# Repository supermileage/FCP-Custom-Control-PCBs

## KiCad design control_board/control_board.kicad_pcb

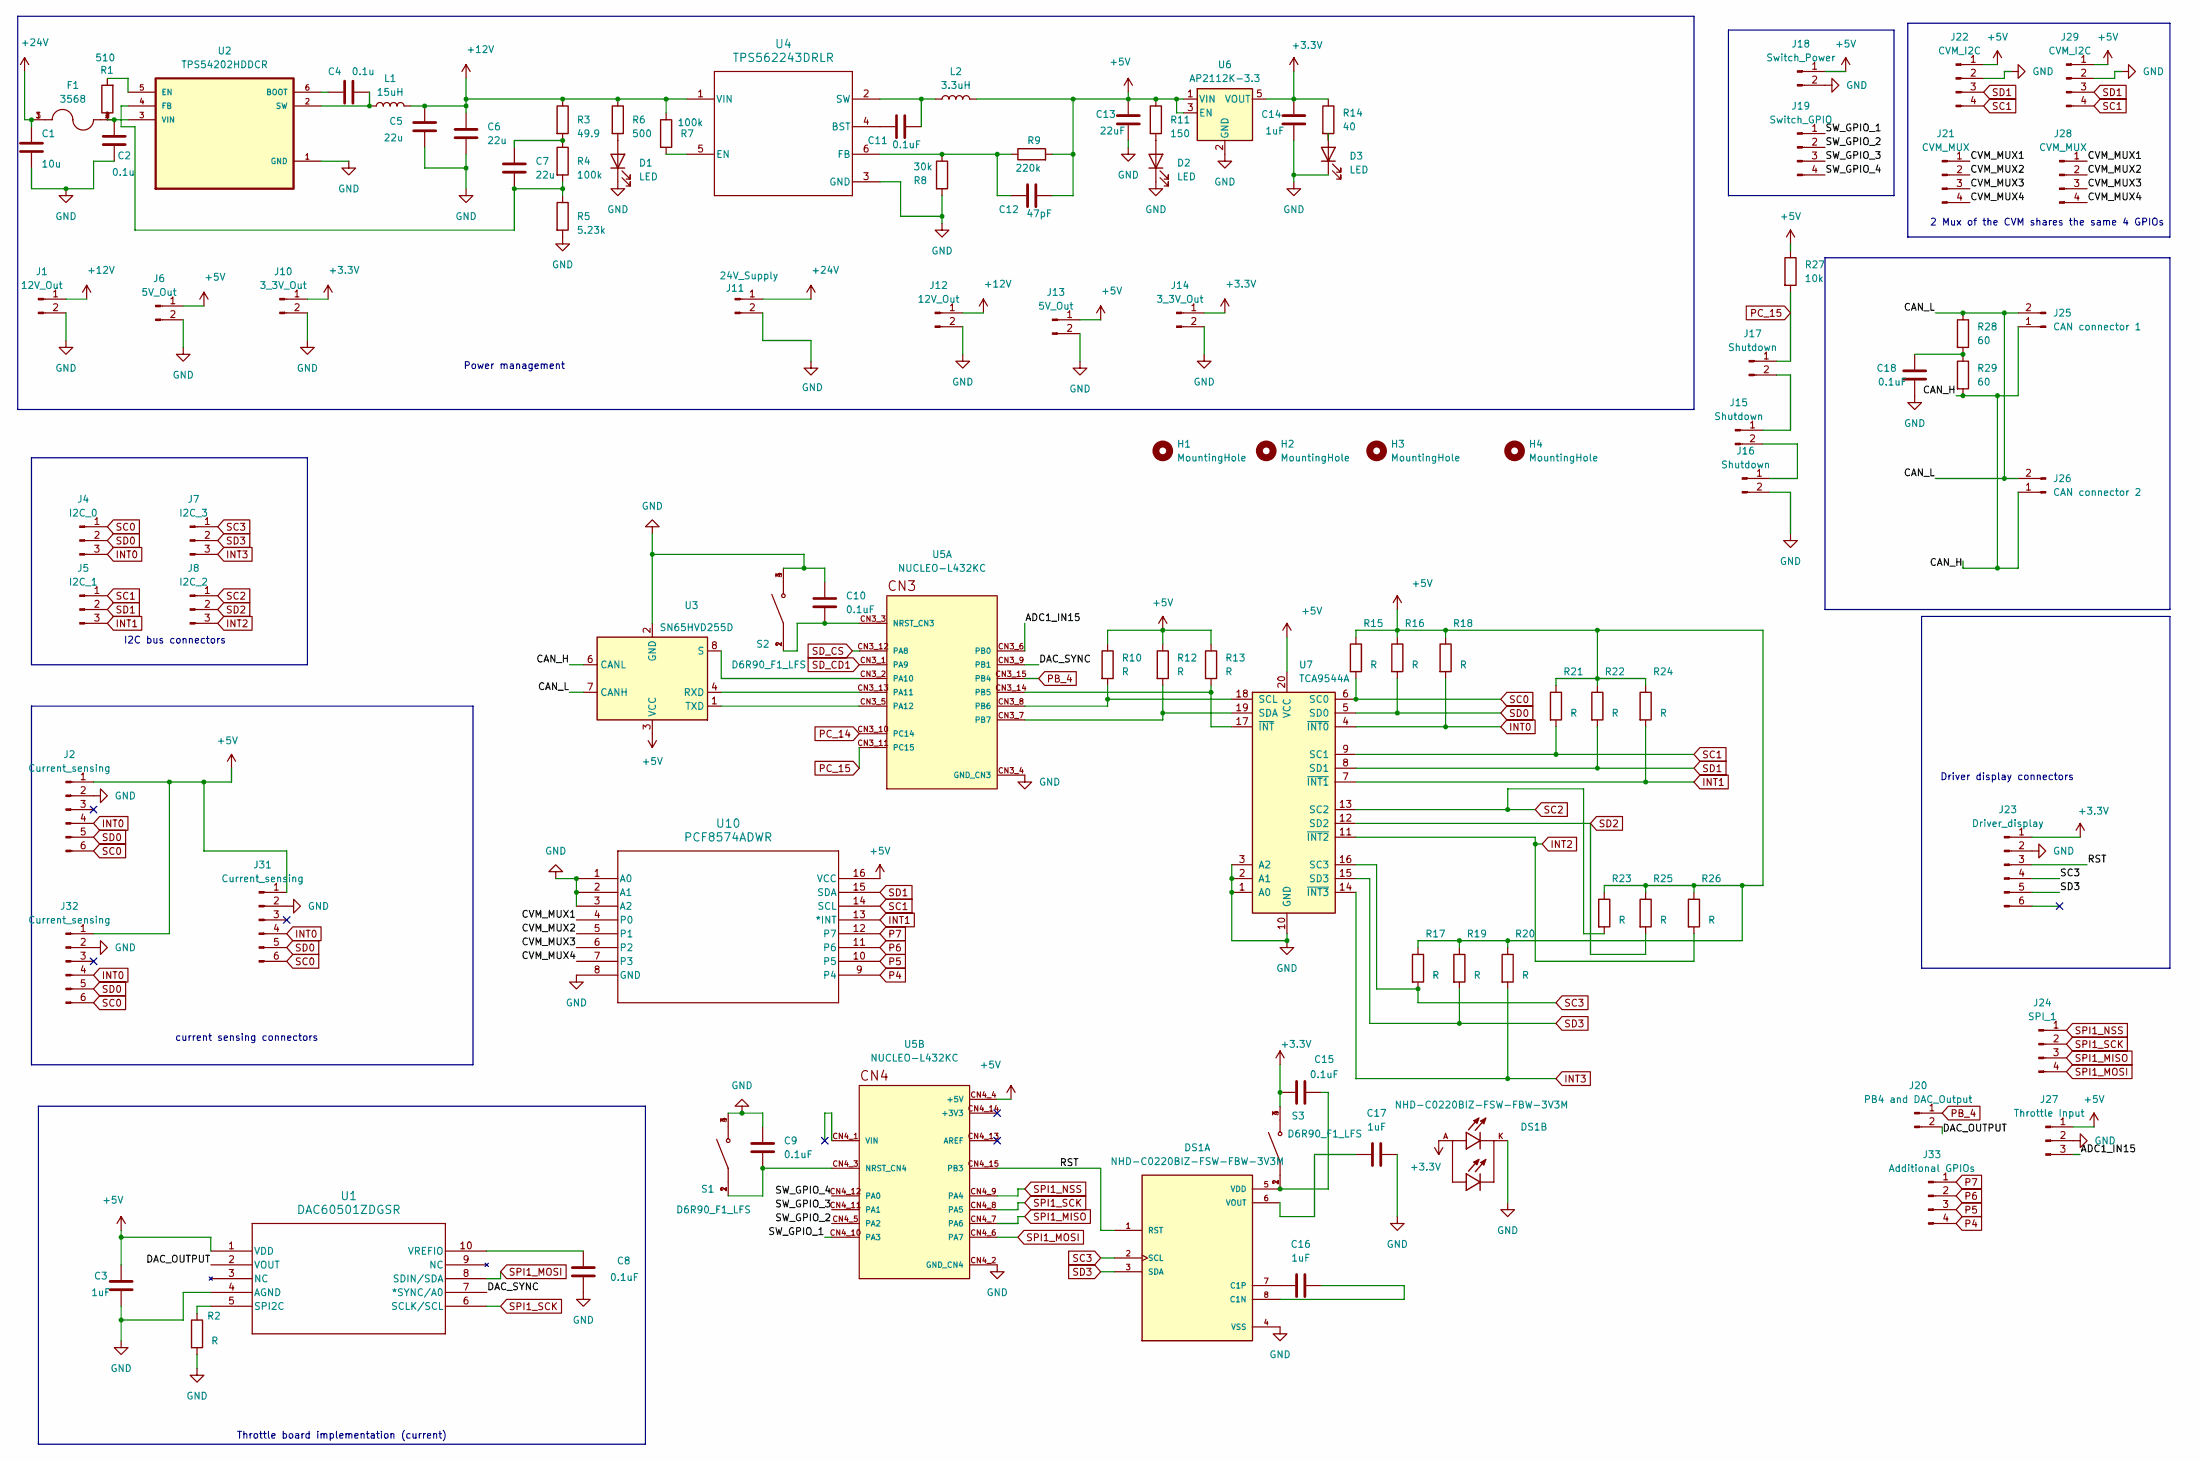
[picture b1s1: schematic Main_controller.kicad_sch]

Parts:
C1: 10u; C_0805_2012Metric
C2, C4: 0.1u; C_0805_2012Metric
C3, C14, C16, C17: 1uF; C_0805_2012Metric
C5, C6, C7: 22u; C_0805_2012Metric
C8, C9, C10, C11, C15, C18: 0.1uF; C_0805_2012Metric
C12: 47pF; C_0805_2012Metric
C13: 22uF; C_0805_2012Metric
D1, D2, D3: LED; LED_0805_2012Metric
DS1: NHD-C0220BIZ-FSW-FBW-3V3M; LCD_NHD-C0220BIZ-FSW-FBW-3V3M; PARTREV 1.0
F1: 3568; FUSE_3568; PARTREV C
H1, H2, H3, H4: MountingHole; MountingHole_5.3mm_M5_DIN965_Pad
J1, J12: 12V_Out; MOLEX_2125280200
J2, J31, J32: Current_sensing; CONN_2125280000_06_MOL
J4: I2C_0; CONN_SDA-70543-xxxx_04_MOL
J5: I2C_1; CONN_SDA-70543-XXXX_03_MOL
J6, J13: 5V_Out; MOLEX_2125280200
J7: I2C_3; CONN_SDA-70543-XXXX_03_MOL
J8: I2C_2; CONN_SDA-70543-XXXX_03_MOL
J10, J14: 3_3V_Out; MOLEX_2125280200
J11: 24V_Supply; MOLEX_2125280200
J15, J16, J17: Shutdown; CONN_SDA-70543-xxxx_02_MOL
J18: Switch_Power; MOLEX_2125280200
J19: Switch_GPIO; CONN_2125280000_04_MOL
J20: PB4 and DAC_Output; MOLEX_2125280200
J21, J28: CVM_MUX; CONN_2125280000_04_MOL
J22, J29: CVM_I2C; CONN_2125280000_04_MOL
J23: Driver_display; CONN_2125280000_06_MOL
J24: SPI_1; CONN_SDA-70543-XXXX_04_MOL
J25: CAN connector 1; MOLEX_2125280200
J26: CAN connector 2; MOLEX_2125280200
J27: Throttle Input; CONN_SDA-70543-XXXX_03_MOL
J33: Additional GPIOs; CONN_SDA-70543-xxxx_04_MOL
L1: 15uH; IND_2012_TDK
L2: 3.3uH; L_1008_2520Metric
R1: 510; R_0805_2012Metric
R2, R10, R12, R13, R15, R16, R17, R18, R19, R20, R21, R22, R23, R24, R25, R26: R; R_0805_2012Metric
R3: 49.9; R_0805_2012Metric
R4, R7: 100k; R_0805_2012Metric
R5: 5.23k; R_0805_2012Metric
R6: 500; R_0805_2012Metric
R8: 30k; R_0805_2012Metric
R9: 220k; R_0805_2012Metric
R11: 150; R_0805_2012Metric
R14: 40; R_0805_2012Metric
R27: 10k; R_0805_2012Metric
R28, R29: 60; R_0805_2012Metric
S1, S2, S3: D6R90_F1_LFS; SW_D6R90_F1_LFS; PARTREV N/A
U1: DAC60501ZDGSR; DGS10_TEX-L
U2: TPS54202HDDCR; SOT95P280X110-6N
U3: SN65HVD255D; SOIC-8_3.9x4.9mm_P1.27mm
U4: TPS562243DRLR; DRL0006A-MFG
U5: NUCLEO-L432KC; MODULE_NUCLEO-L432KC; PARTREV N/A; DigiKey_Part_Number 497-16592-ND
U6: AP2112K-3.3; SOT-23-5
U7: TCA9544A; TSSOP-20_4.4x6.5mm_P0.65mm
U10: PCF8574ADWR; DW16

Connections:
+3.3V: C14.1, C15.2, DS1.A, J10.1, J14.1, J23.1, R14.1, S3.3, S3.4, U6.5 (VOUT); also elsewhere on the board
+5V: C3.2, C12.2, C13.1, J2.1, J6.1, J13.1, J18.1, J22.1, J27.1, J29.1, J31.1, J32.1, L2.2, R9.2, R10.1, R11.1, R12.1, R13.1, R15.1, R16.1, R17.1, R18.1, R19.1, R20.1, R21.1, R22.1, R23.1, R24.1, R25.1, R26.1, R27.1, U1.1 (VDD), U3.3 (VCC), U5.CN4_4 (+5V), U6.1 (VIN), U6.3 (EN), U7.20 (VCC), U10.16 (VCC); also elsewhere on the board
+12V: C5.1, C6.1, J1.1, J12.1, L1.2, R3.1, R6.1, R7.1, U4.1 (VIN)
+24V: C1.1, F1.1, F1.3, J11.1
/Main_controller/ADC1_IN15: J27.3, U5.CN3_6 (PB0)
/Main_controller/CAN_H: J25.1, J26.1, R29.2, U3.6 (CANL)
/Main_controller/CAN_L: J25.2, J26.2, R28.1, U3.7 (CANH)
/Main_controller/CVM_MUX1: J21.1, J28.1, U10.4 (P0)
/Main_controller/CVM_MUX2: J21.2, J28.2, U10.5 (P1)
/Main_controller/CVM_MUX3: J21.3, J28.3, U10.6 (P2)
/Main_controller/CVM_MUX4: J21.4, J28.4, U10.7 (P3)
/Main_controller/DAC_OUTPUT: J20.2, U1.2 (VOUT)
/Main_controller/DAC_SYNC: U1.7 (*SYNC/A0), U5.CN3_9 (PB1)
/Main_controller/RST: DS1.1 (RST), J23.3, U5.CN4_15 (PB3)
/Main_controller/SW_GPIO_1: J19.1, U5.CN4_10 (PA3)
/Main_controller/SW_GPIO_2: J19.2, U5.CN4_5 (PA2)
/Main_controller/SW_GPIO_3: J19.3, U5.CN4_11 (PA1)
/Main_controller/SW_GPIO_4: J19.4, U5.CN4_12 (PA0)
GND: C1.2, C2.2, C3.1, C5.2, C6.2, C8.1, C9.2, C10.2, C13.2, C14.2, C17.2, C18.2, D1.1 (K), D2.1 (K), D3.1 (K), DS1.4 (VSS), DS1.K, J1.2, J2.2, J6.2, J10.2, J11.2, J12.2, J13.2, J14.2, J16.2, J18.2, J22.2, J23.2, J27.2, J29.2, J31.2, J32.2, R2.2, R5.2, R8.2, S1.3, S1.4, S2.3, S2.4, U1.4 (AGND), U2.1 (GND), U3.2 (GND), U4.3 (GND), U5.CN3_4 (GND_CN3), U5.CN4_2 (GND_CN4), U6.2 (GND), U7.1 (A0), U7.2 (A1), U7.3 (A2), U7.10 (GND), U10.1 (A0), U10.2 (A1), U10.3 (A2), U10.8 (GND); also elsewhere on the board
INT0: J2.4, J4.3, J31.4, J32.4, R18.2, U7.4 (~INT0)
INT1: J5.3, R24.2, U7.7 (~INT1), U10.13 (*INT)
INT2: J8.3, R26.2, U7.11 (~INT2)
INT3: J7.3, R20.2, U7.14 (~INT3)
unnamed: C7.1, R3.2, R4.1
unnamed: C18.1, R28.2, R29.1
unnamed: D1.2 (A), R6.2
unnamed: D2.2 (A), R11.2
unnamed: D3.2 (A), R14.2
unnamed: C16.2, DS1.8 (C1N)
unnamed: C16.1, DS1.7 (C1P)
unnamed: C15.1, DS1.5 (VDD), S3.1, S3.2
unnamed: C17.1, DS1.6 (VOUT)
unnamed: J15.1, J17.2
unnamed: J15.2, J16.1
unnamed: R2.1, U1.5 (SPI2C)
unnamed: C8.2, U1.10 (VREFIO)
unnamed: C4.1, U2.6 (BOOT)
unnamed: R1.2, U2.5 (EN)
unnamed: C7.2, R4.2, R5.1, U2.4 (FB)
unnamed: C4.2, L1.1, U2.2 (SW)
unnamed: C2.1, F1.2, F1.4, R1.1, U2.3 (VIN)
unnamed: U3.4 (RXD), U5.CN3_13 (PA11)
unnamed: U3.8 (S), U5.CN3_2 (PA10)
unnamed: U3.1 (TXD), U5.CN3_5 (PA12)
unnamed: C11.1, U4.4 (BST)
unnamed: R7.2, U4.5 (EN)
unnamed: C12.1, R8.1, R9.1, U4.6 (FB)
unnamed: C11.2, L2.1, U4.2 (SW)
unnamed: C10.1, S2.1, S2.2, U5.CN3_3 (NRST_CN3)
unnamed: R13.2, U5.CN3_14 (PB5), U7.17 (~INT)
unnamed: R10.2, U5.CN3_8 (PB6), U7.18 (SCL)
unnamed: R12.2, U5.CN3_7 (PB7), U7.19 (SDA)
unnamed: C9.1, S1.1, S1.2, U5.CN4_3 (NRST_CN4)
P4: J33.4, U10.9 (P4)
P5: J33.3, U10.10 (P5)
P6: J33.2, U10.11 (P6)
P7: J33.1, U10.12 (P7)
PB_4: J20.1, U5.CN3_15 (PB4)
PC_14: U5.CN3_10 (PC14); also elsewhere on the board
PC_15: J17.1, R27.2, U5.CN3_11 (PC15)
SC0: J2.6, J4.1, J31.6, J32.6, R15.2, U7.6 (SC0)
SC1: J5.1, J22.4, J29.4, R21.2, U7.9 (SC1), U10.14 (SCL)
SC2: J8.1, R23.2, U7.13 (SC2); also elsewhere on the board
SC3: DS1.2 (SCL), J7.1, J23.4, R17.2, U7.16 (SC3)
SD0: J2.5, J4.2, J31.5, J32.5, R16.2, U7.5 (SD0)
SD1: J5.2, J22.3, J29.3, R22.2, U7.8 (SD1), U10.15 (SDA)
SD2: J8.2, R25.2, U7.12 (SD2); also elsewhere on the board
SD3: DS1.3 (SDA), J7.2, J23.5, R19.2, U7.15 (SD3)
SD_CD1: U5.CN3_1 (PA9); also elsewhere on the board
SD_CS: U5.CN3_12 (PA8); also elsewhere on the board
SPI1_MISO: J24.3, U5.CN4_7 (PA6); also elsewhere on the board
SPI1_MOSI: J24.4, U1.8 (SDIN/SDA), U5.CN4_6 (PA7); also elsewhere on the board
SPI1_NSS: J24.1, U5.CN4_9 (PA4)
SPI1_SCK: J24.2, U1.6 (SCLK/SCL), U5.CN4_8 (PA5); also elsewhere on the board

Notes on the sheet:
I2C bus connectors
Power management
current sensing connectors
Driver display connectors
2 Mux of the CVM shares the same 4 GPIOs
Throttle board implementation (current)

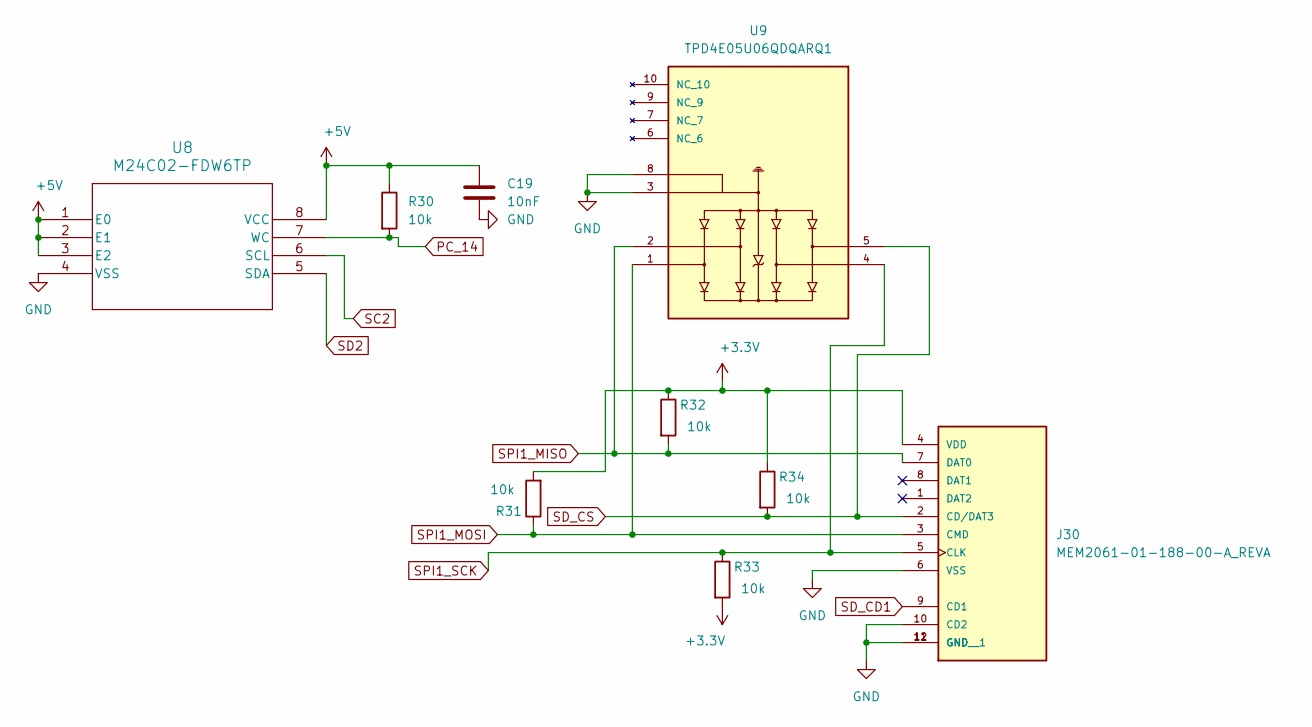
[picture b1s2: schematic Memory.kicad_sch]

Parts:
C19: 10nF; C_0805_2012Metric
J30: MEM2061-01-188-00-A_REVA; GCT_MEM2061-01-188-00-A_REVA
R30, R31, R32, R33, R34: 10k; R_0805_2012Metric
U8: M24C02-FDW6TP; TSSOP8_M24C02_STM
U9: TPD4E05U06QDQARQ1; IC_TPD4E05U06QDQARQ1; PARTREV F

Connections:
+3.3V: J30.4 (VDD), R31.2, R32.1, R33.2, R34.1; also elsewhere on the board
+5V: C19.1, R30.1, U8.1 (E0), U8.2 (E1), U8.3 (E2), U8.8 (VCC); also elsewhere on the board
GND: C19.2, J30.6 (VSS), J30.10 (CD2), J30.11 (GND), J30.12 (GND__1), U8.4 (VSS), U9.3, U9.8; also elsewhere on the board
PC_14: R30.2, U8.7 (WC); also elsewhere on the board
SC2: U8.6 (SCL); also elsewhere on the board
SD2: U8.5 (SDA); also elsewhere on the board
SD_CD1: J30.9 (CD1); also elsewhere on the board
SD_CS: J30.2 (CD/DAT3), R34.2, U9.5; also elsewhere on the board
SPI1_MISO: J30.7 (DAT0), R32.2, U9.2; also elsewhere on the board
SPI1_MOSI: J30.3 (CMD), R31.1, U9.1; also elsewhere on the board
SPI1_SCK: J30.5 (CLK), R33.1, U9.4; also elsewhere on the board

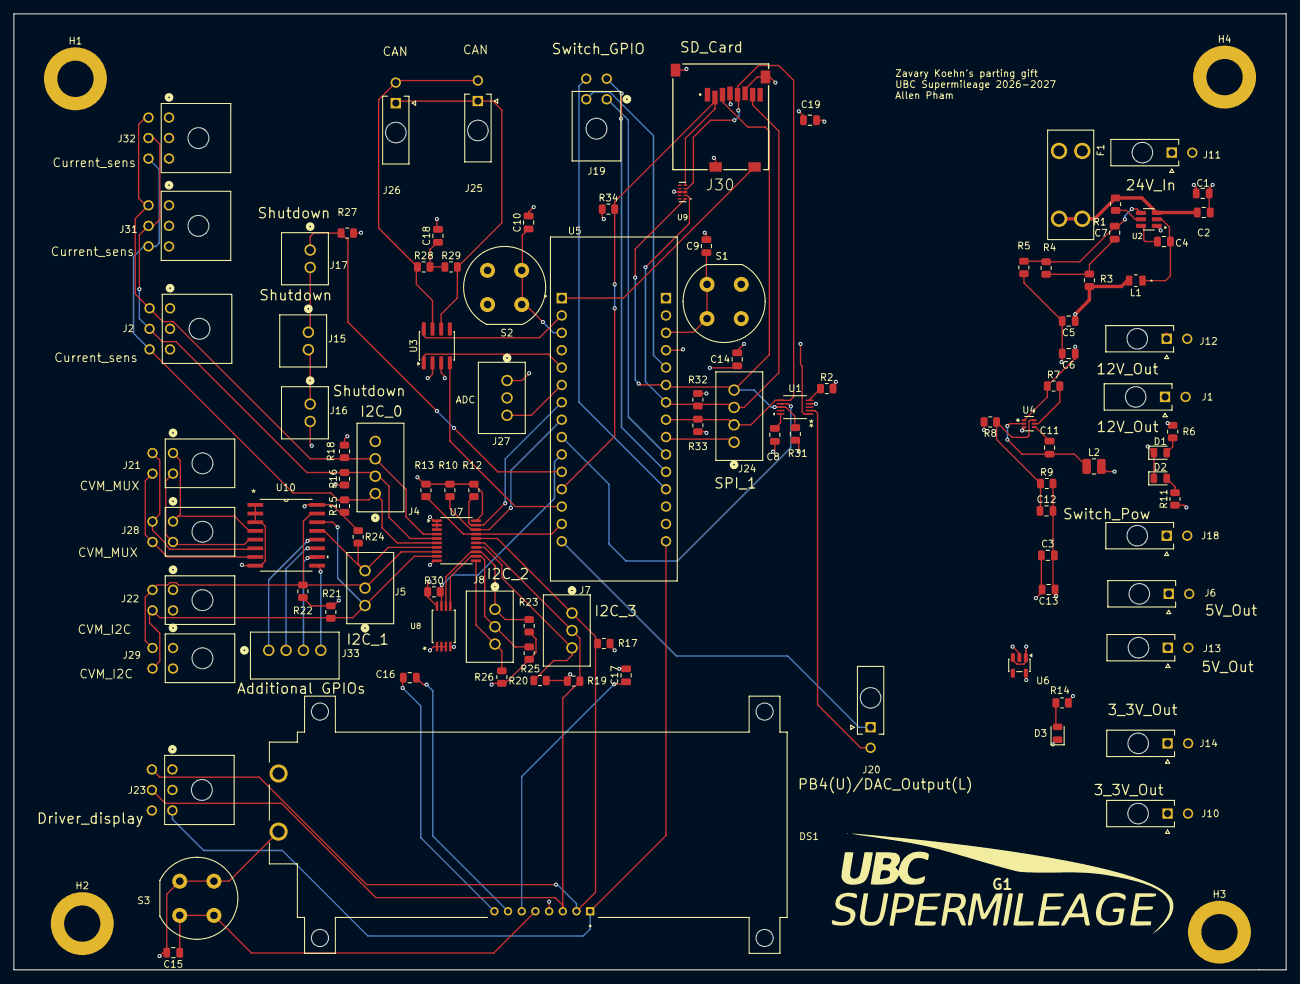
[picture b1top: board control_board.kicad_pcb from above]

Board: 4 copper layers, 186.0 x 139.8 mm, 109 parts (0 on the bottom side), 74 nets.

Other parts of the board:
G1: LOGO

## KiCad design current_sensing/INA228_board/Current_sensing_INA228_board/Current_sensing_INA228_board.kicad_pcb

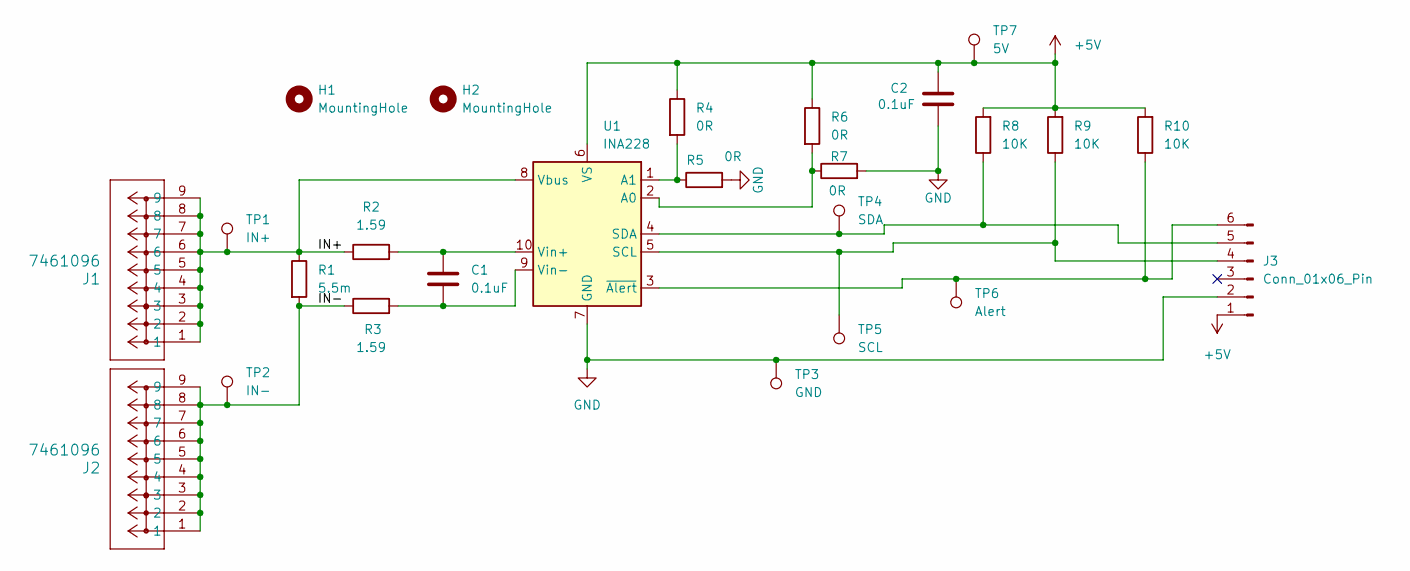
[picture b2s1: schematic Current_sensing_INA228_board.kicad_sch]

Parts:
C1, C2: 0.1uF; C_0402_1005Metric
H1, H2: MountingHole; MountingHole_4.3mm_M4_DIN965
J1, J2: 7461096; CONN9_1096_WRE
J3: Conn_01x06_Pin; CONN_2125280000_06_MOL
R1: 5.5m; R_0603_1608Metric
R2, R3: 1.59; R_0603_1608Metric
R4, R5, R6, R7: 0R; R_0603_1608Metric
R8, R9, R10: 10K; R_0603_1608Metric
TP1: IN+; TestPoint_Keystone_5000-5004_Miniature
TP2: IN-; TestPoint_Keystone_5000-5004_Miniature
TP3: GND; TestPoint_Keystone_5000-5004_Miniature
TP4: SDA; TestPoint_Keystone_5000-5004_Miniature
TP5: SCL; TestPoint_Keystone_5000-5004_Miniature
TP6: Alert; TestPoint_Keystone_5000-5004_Miniature
TP7: 5V; TestPoint_Keystone_5000-5004_Miniature
U1: INA228; VSSOP-10_3x3mm_P0.5mm

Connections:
+5V: C2.1, J3.1, R4.1, R6.1, R8.2, R9.2, R10.2, TP7.1, U1.6 (VS)
/IN+: J1.1, J1.2, J1.3, J1.4, J1.5, J1.6, J1.7, J1.8, J1.9, R1.1, R2.1, TP1.1, U1.8 (Vbus)
/IN-: J2.1, J2.2, J2.3, J2.4, J2.5, J2.6, J2.7, J2.8, J2.9, R1.2, R3.1, TP2.1
GND: C2.2, J3.2, R5.2, R7.2, TP3.1, U1.7 (GND)
unnamed: J3.4, R9.1, TP5.1, U1.5 (SCL)
unnamed: J3.5, R8.1, TP4.1, U1.4 (SDA)
unnamed: J3.6, R10.1, TP6.1, U1.3 (~Alert)
unnamed: R6.2, R7.1, U1.2 (A0)
unnamed: R4.2, R5.1, U1.1 (A1)
unnamed: C1.1, R2.2, U1.10 (Vin+)
unnamed: C1.2, R3.2, U1.9 (Vin-)

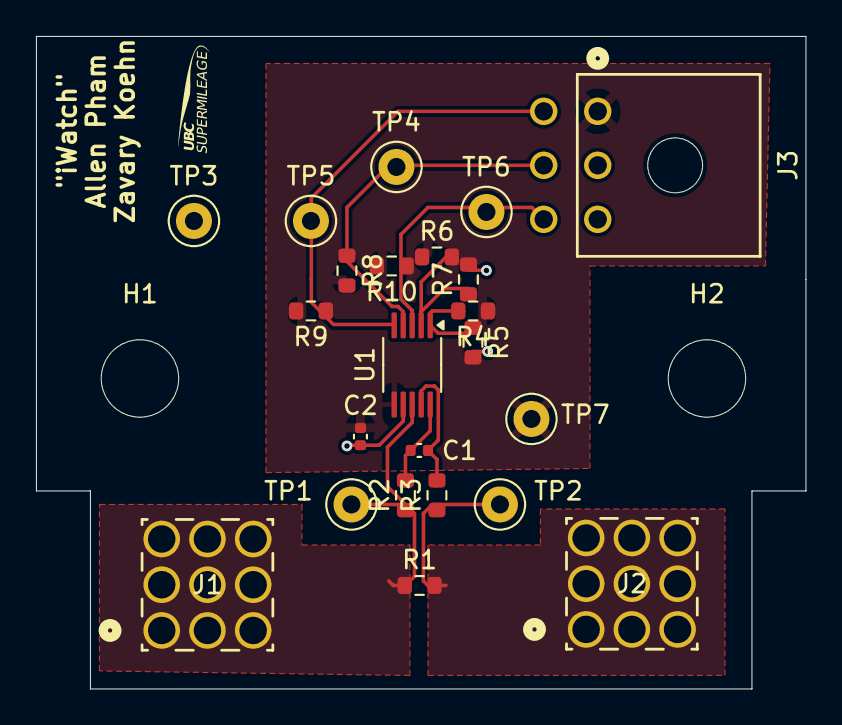
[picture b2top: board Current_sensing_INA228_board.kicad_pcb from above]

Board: 2 copper layers, 42.8 x 36.2 mm, 25 parts (0 on the bottom side), 11 nets.

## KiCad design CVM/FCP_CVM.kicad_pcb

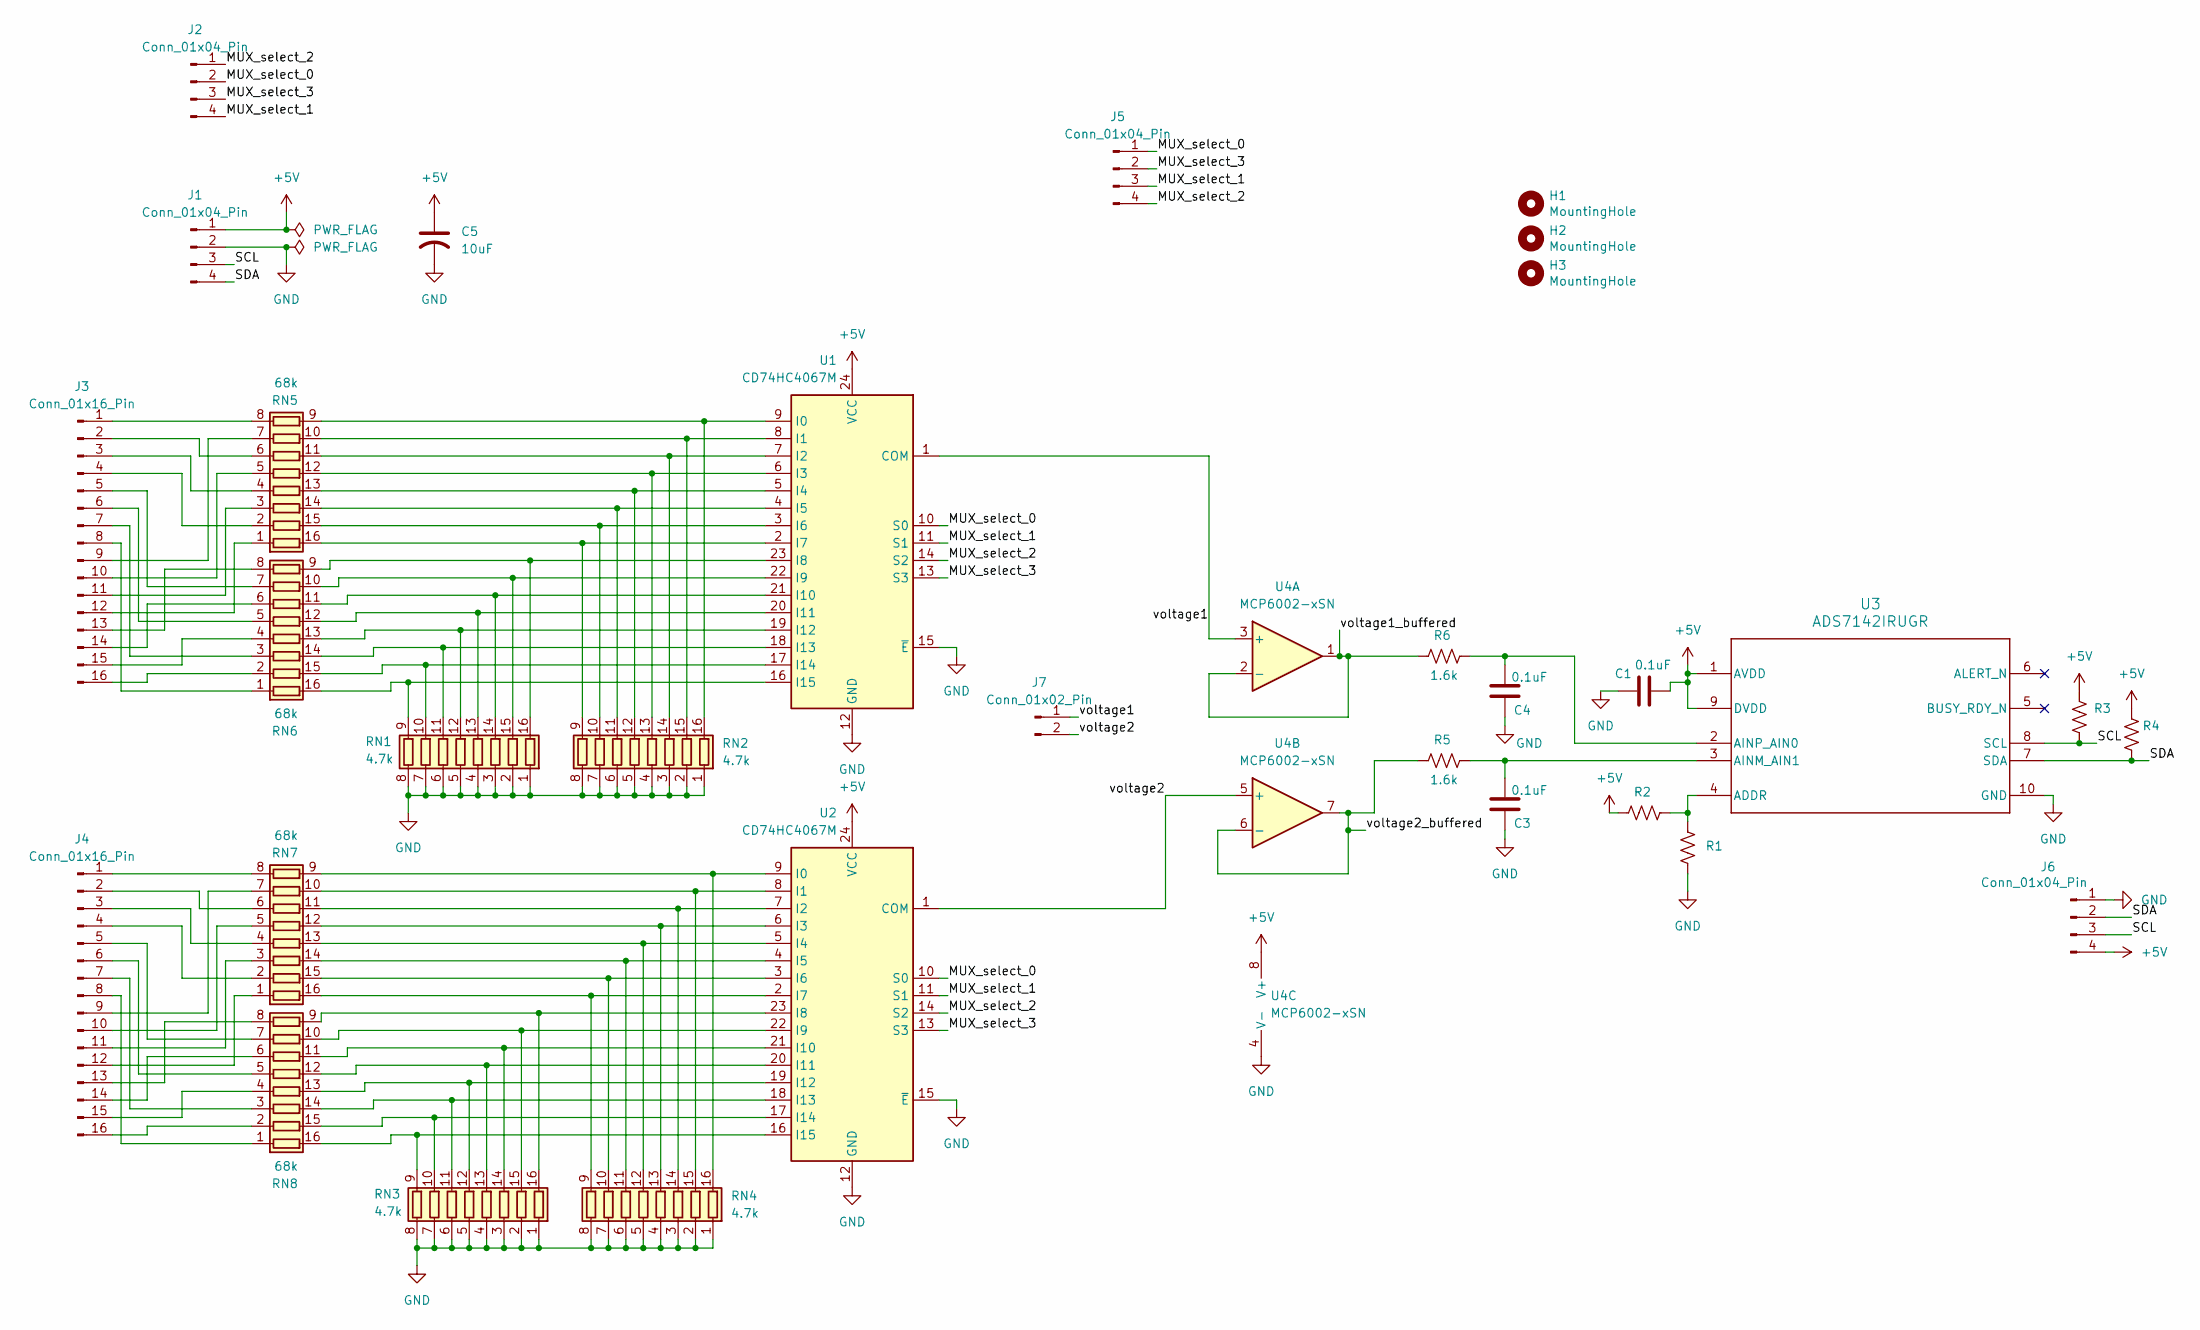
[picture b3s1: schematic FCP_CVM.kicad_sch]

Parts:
C1, C3, C4: 0.1uF; C_0805_2012Metric_Pad1.18x1.45mm_HandSolder
C5: 10uF; WCAP-ASLI_4X5.5_DXL_
H1, H2, H3: MountingHole; MountingHole_3.2mm_M3
J1, J2: Conn_01x04_Pin; MOLEX_2125280400
J3, J4: Conn_01x16_Pin; AMPHENOL_10127720-162LF
J5, J6: Conn_01x04_Pin; PinHeader_1x04_P2.54mm_Vertical
J7: Conn_01x02_Pin; PinHeader_1x02_P2.54mm_Vertical
R1, R2, R3, R4: R_US; R_0805_2012Metric_Pad1.20x1.40mm_HandSolder
R5, R6: 1.6k; R_0805_2012Metric_Pad1.20x1.40mm_HandSolder
RN1, RN2, RN3, RN4: 4.7k; RES_EXB2HV
RN5, RN6, RN7, RN8: 68k; RES_EXB2HV
U1, U2: CD74HC4067M; SOIC-24W_7.5x15.4mm_P1.27mm
U3: ADS7142IRUGR; RUG0010A
U4: MCP6002-xSN; SOIC-8_3.9x4.9mm_P1.27mm

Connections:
+5V: C1.1, C5.1, J1.1, J6.4, R2.2, R3.1, R4.1, U1.24 (VCC), U2.24 (VCC), U3.1 (AVDD), U3.9 (DVDD), U4.8 (V+)
/MUX_select_0: J2.2, J5.1, U1.10 (S0), U2.10 (S0)
/MUX_select_1: J2.4, J5.3, U1.11 (S1), U2.11 (S1)
/MUX_select_2: J2.1, J5.4, U1.14 (S2), U2.14 (S2)
/MUX_select_3: J2.3, J5.2, U1.13 (S3), U2.13 (S3)
/SCL: J1.3, J6.3, R3.2, U3.8 (SCL)
/SDA: J1.4, J6.2, R4.2, U3.7 (SDA)
/voltage1: J7.1, U1.1 (COM), U4.3 (+)
/voltage1_buffered: R6.2, U4.1, U4.2 (-)
/voltage2: J7.2, U2.1 (COM), U4.5 (+)
/voltage2_buffered: R5.2, U4.6 (-), U4.7
GND: C1.2, C3.2, C4.2, C5.2, J1.2, J6.1, R1.2, RN1.1 (R1.1), RN1.2 (R2.1), RN1.3 (R3.1), RN1.4 (R4.1), RN1.5 (R5.1), RN1.6 (R6.1), RN1.7 (R7.1), RN1.8 (R8.1), RN2.1 (R1.1), RN2.2 (R2.1), RN2.3 (R3.1), RN2.4 (R4.1), RN2.5 (R5.1), RN2.6 (R6.1), RN2.7 (R7.1), RN2.8 (R8.1), RN3.1 (R1.1), RN3.2 (R2.1), RN3.3 (R3.1), RN3.4 (R4.1), RN3.5 (R5.1), RN3.6 (R6.1), RN3.7 (R7.1), RN3.8 (R8.1), RN4.1 (R1.1), RN4.2 (R2.1), RN4.3 (R3.1), RN4.4 (R4.1), RN4.5 (R5.1), RN4.6 (R6.1), RN4.7 (R7.1), RN4.8 (R8.1), U1.12 (GND), U1.15 (~E), U2.12 (GND), U2.15 (~E), U3.10 (GND), U4.4 (V-)
unnamed: J3.1, RN5.8 (R8.1)
unnamed: J3.2, RN5.6 (R6.1)
unnamed: J3.3, RN5.4 (R4.1)
unnamed: J3.4, RN5.2 (R2.1)
unnamed: J3.5, RN6.7 (R7.1)
unnamed: J3.6, RN6.5 (R5.1)
unnamed: J3.7, RN6.3 (R3.1)
unnamed: J3.8, RN6.1 (R1.1)
unnamed: J3.9, RN5.7 (R7.1)
unnamed: J3.10, RN5.5 (R5.1)
unnamed: J3.11, RN5.3 (R3.1)
unnamed: J3.12, RN5.1 (R1.1)
unnamed: J3.13, RN6.8 (R8.1)
unnamed: J3.14, RN6.6 (R6.1)
unnamed: J3.15, RN6.4 (R4.1)
unnamed: J3.16, RN6.2 (R2.1)
unnamed: J4.1, RN7.8 (R8.1)
unnamed: J4.2, RN7.6 (R6.1)
unnamed: J4.3, RN7.4 (R4.1)
unnamed: J4.4, RN7.2 (R2.1)
unnamed: J4.5, RN8.7 (R7.1)
unnamed: J4.6, RN8.5 (R5.1)
unnamed: J4.7, RN8.3 (R3.1)
unnamed: J4.8, RN8.1 (R1.1)
unnamed: J4.9, RN7.7 (R7.1)
unnamed: J4.10, RN7.5 (R5.1)
unnamed: J4.11, RN7.3 (R3.1)
unnamed: J4.12, RN7.1 (R1.1)
unnamed: J4.13, RN8.8 (R8.1)
unnamed: J4.14, RN8.6 (R6.1)
unnamed: J4.15, RN8.4 (R4.1)
unnamed: J4.16, RN8.2 (R2.1)
unnamed: RN1.16 (R1.2), RN6.9 (R8.2), U1.23 (I8)
unnamed: RN1.15 (R2.2), RN6.10 (R7.2), U1.22 (I9)
unnamed: RN1.14 (R3.2), RN6.11 (R6.2), U1.21 (I10)
unnamed: RN1.13 (R4.2), RN6.12 (R5.2), U1.20 (I11)
unnamed: RN1.12 (R5.2), RN6.13 (R4.2), U1.19 (I12)
unnamed: RN1.11 (R6.2), RN6.14 (R3.2), U1.18 (I13)
unnamed: RN1.10 (R7.2), RN6.15 (R2.2), U1.17 (I14)
unnamed: RN1.9 (R8.2), RN6.16 (R1.2), U1.16 (I15)
unnamed: RN2.16 (R1.2), RN5.9 (R8.2), U1.9 (I0)
unnamed: RN2.15 (R2.2), RN5.10 (R7.2), U1.8 (I1)
unnamed: RN2.14 (R3.2), RN5.11 (R6.2), U1.7 (I2)
unnamed: RN2.13 (R4.2), RN5.12 (R5.2), U1.6 (I3)
unnamed: RN2.12 (R5.2), RN5.13 (R4.2), U1.5 (I4)
unnamed: RN2.11 (R6.2), RN5.14 (R3.2), U1.4 (I5)
unnamed: RN2.10 (R7.2), RN5.15 (R2.2), U1.3 (I6)
unnamed: RN2.9 (R8.2), RN5.16 (R1.2), U1.2 (I7)
unnamed: RN3.16 (R1.2), RN8.9 (R8.2), U2.23 (I8)
unnamed: RN3.15 (R2.2), RN8.10 (R7.2), U2.22 (I9)
unnamed: RN3.14 (R3.2), RN8.11 (R6.2), U2.21 (I10)
unnamed: RN3.13 (R4.2), RN8.12 (R5.2), U2.20 (I11)
unnamed: RN3.12 (R5.2), RN8.13 (R4.2), U2.19 (I12)
unnamed: RN3.11 (R6.2), RN8.14 (R3.2), U2.18 (I13)
unnamed: RN3.10 (R7.2), RN8.15 (R2.2), U2.17 (I14)
unnamed: RN3.9 (R8.2), RN8.16 (R1.2), U2.16 (I15)
unnamed: RN4.16 (R1.2), RN7.9 (R8.2), U2.9 (I0)
unnamed: RN4.15 (R2.2), RN7.10 (R7.2), U2.8 (I1)
unnamed: RN4.14 (R3.2), RN7.11 (R6.2), U2.7 (I2)
unnamed: RN4.13 (R4.2), RN7.12 (R5.2), U2.6 (I3)
unnamed: RN4.12 (R5.2), RN7.13 (R4.2), U2.5 (I4)
unnamed: RN4.11 (R6.2), RN7.14 (R3.2), U2.4 (I5)
unnamed: RN4.10 (R7.2), RN7.15 (R2.2), U2.3 (I6)
unnamed: RN4.9 (R8.2), RN7.16 (R1.2), U2.2 (I7)
unnamed: R1.1, R2.1, U3.4 (ADDR)
unnamed: C3.1, R5.1, U3.3 (AINM_AIN1)
unnamed: C4.1, R6.1, U3.2 (AINP_AIN0)

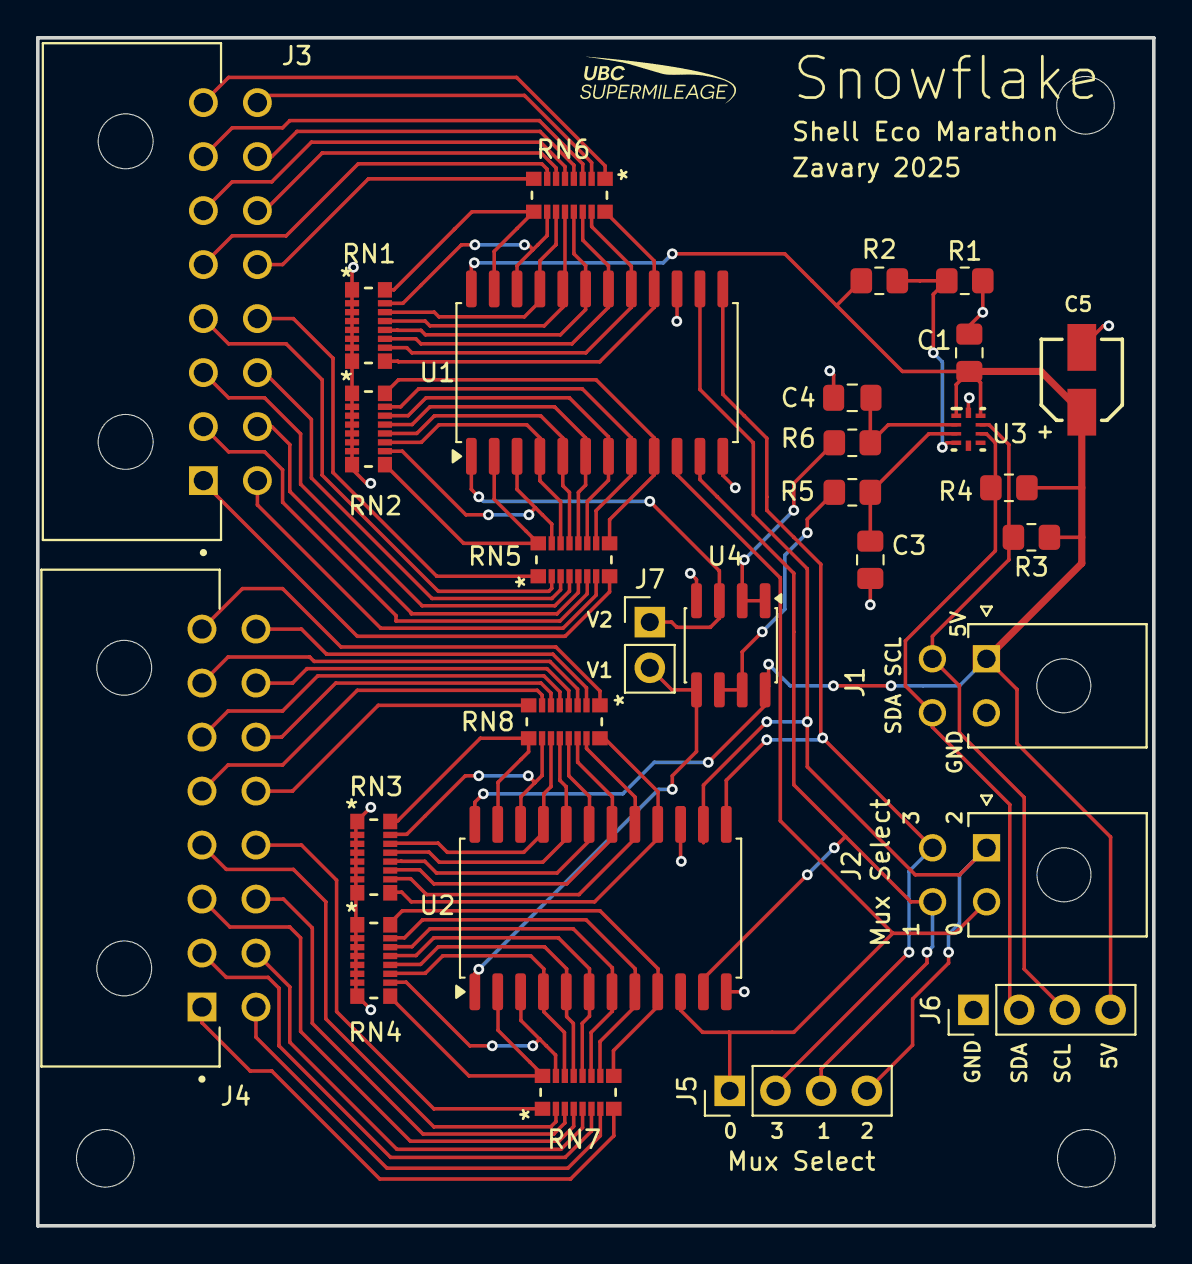
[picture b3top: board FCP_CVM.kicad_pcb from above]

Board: 2 copper layers, 62.0 x 66.0 mm, 32 parts (0 on the bottom side), 79 nets.

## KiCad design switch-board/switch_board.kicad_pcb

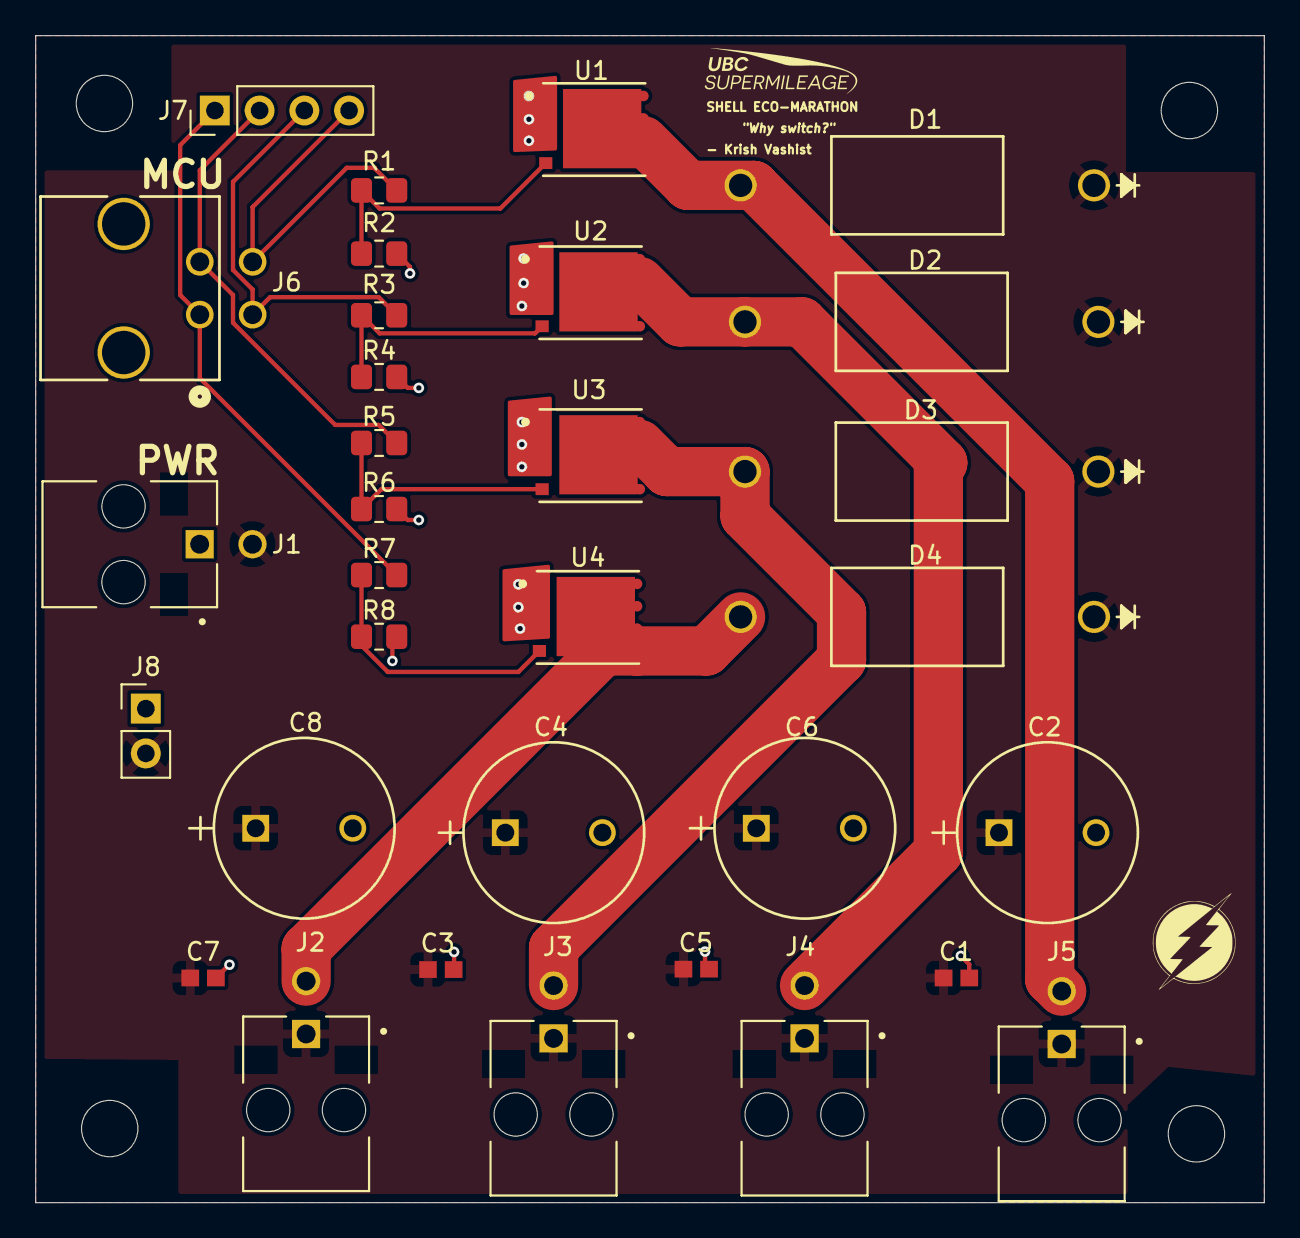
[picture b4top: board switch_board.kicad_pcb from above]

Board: 2 copper layers, 69.8 x 66.3 mm, 36 parts (0 on the bottom side), 14 nets.

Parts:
C1, C3, C5, C7: 0.1 μ; CAPC17595_95N_KEM
C2, C4, C6, C8: 200 μ; PCAP_10x16-THRU-ELECT_NCA
D1, D2, D3, D4: D; CR_30-E3&slash_54_VIS
H3, H3#2, H3#3, H3#4: MountingHole; MountingHole_3.2mm_M3
J1, J2, J3, J4, J5: 43045-0221; MOLEX_43045-0221
J6: 430450421; CONN_SD-43045-008_04_MOL
J7: Conn_01x04_Pin; PinHeader_1x04_P2.54mm_Vertical
J8: Conn_01x02_Pin; PinHeader_1x02_P2.54mm_Vertical
R1, R3, R5, R7: 100; R_0805_2012Metric_Pad1.20x1.40mm_HandSolder
R2, R4, R6, R8: 100k; R_0805_2012Metric_Pad1.20x1.40mm_HandSolder
U1, U2, U3, U4: CSD17578Q5A; DQJ0008A-MFG

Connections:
+VDC: C1.1, C2.1, C3.1, C4.1, C5.1, C6.1, C7.1, C8.1, D1.1 (K), D2.1 (K), D3.1 (K), D4.1 (K), J1.2, J2.1, J3.1, J4.1, J5.1, J8.2
/Drain_Q1: D1.2 (A), J5.2, U1.5 (D), U1.6 (D), U1.7 (D), U1.8 (D)
/Drain_Q2: D2.2 (A), J4.2, U2.5 (D), U2.6 (D), U2.7 (D), U2.8 (D)
/Drain_Q3: D3.2 (A), J3.2, U3.5 (D), U3.6 (D), U3.7 (D), U3.8 (D)
/Drain_Q4: D4.2 (A), J2.2, U4.5 (D), U4.6 (D), U4.7 (D), U4.8 (D)
/mcu_p1: J6.1, J7.1, R7.1
/mcu_p2: J6.2, J7.2, R5.1
/mcu_p3: J6.3, J7.3, R3.1
/mcu_p4: J6.4, J7.4, R1.1
GND: C1.2, C2.2, C3.2, C4.2, C5.2, C6.2, C7.2, C8.2, J1.1, J8.1, R2.1, R4.1, R6.1, R8.1, U1.1 (S), U1.2 (S), U1.3 (S), U2.1 (S), U2.2 (S), U2.3 (S), U3.1 (S), U3.2 (S), U3.3 (S), U4.1 (S), U4.2 (S), U4.3 (S)
unnamed: R1.2, R2.2, U1.4 (G)
unnamed: R3.2, R4.2, U2.4 (G)
unnamed: R5.2, R6.2, U3.4 (G)
unnamed: R7.2, R8.2, U4.4 (G)

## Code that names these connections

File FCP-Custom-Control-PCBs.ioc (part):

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Mcu.Name=STM32L432K(B-C)Ux
Mcu.Package=UFQFPN32
Mcu.UserName=STM32L432KCUx
PA0.Signal=GPIO_Output
PA1.Signal=GPIO_Output
PA11.Mode=CAN_Activate
PA11.Signal=CAN1_RX
PA12.Mode=CAN_Activate
PA12.Signal=CAN1_TX
PA13\ (JTMS-SWDIO).Mode=Serial_Wire
PA13\ (JTMS-SWDIO).Signal=SYS_JTMS-SWDIO
PA14\ (JTCK-SWCLK).Mode=Serial_Wire
PA14\ (JTCK-SWCLK).Signal=SYS_JTCK-SWCLK
PA2.Signal=GPIO_Output
PA3.Signal=GPIO_Output
PA4.Mode=NSS_Signal_Hard_Output
PA4.Signal=SPI1_NSS
PA5.Mode=Full_Duplex_Master
PA5.Signal=SPI1_SCK
PA6.Mode=Full_Duplex_Master
PA6.Signal=SPI1_MISO
PA7.Mode=Full_Duplex_Master
PA7.Signal=SPI1_MOSI
PB0.Signal=ADCx_IN15
PB1.GPIOParameters=GPIO_Label
PB1.GPIO_Label=DAC_SYNC
PB1.Signal=GPIO_Output
PB3\ (JTDO-TRACESWO).Signal=COMP2_INM
PB5.GPIOParameters=GPIO_Speed
PB5.GPIO_Speed=GPIO_SPEED_FREQ_VERY_HIGH
PB5.Mode=SMBus-Alert-mode
PB5.Signal=I2C1_SMBA
PB6.GPIOParameters=GPIO_FM6
PB6.GPIO_FM6=SYSCFG_FASTMODEPLUS_PB6
PB6.Mode=SMBus-Alert-mode
PB6.Signal=I2C1_SCL
PB7.GPIOParameters=GPIO_FM7
PB7.GPIO_FM7=SYSCFG_FASTMODEPLUS_PB7
PB7.Mode=SMBus-Alert-mode
PB7.Signal=I2C1_SDA
RCC.HSE_VALUE=8000000
board=custom

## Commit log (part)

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2025-11-25 added file structure
2025-11-29 Add my project into current sensing
2025-11-30 Add INA228 current sensing board project
2025-12-04 update with the silkscreen for testpoints
2025-12-04 double check on the testpoints, correct labelling
2026-01-20 final small mods before ordering
2026-01-20 fixed folder structure
2026-02-23 Control Board schematics
2026-03-14 Add testing_switchboard for MOSFET switching
    This file tests the switching ability of MOSFETs by toggling an LED on and off every 0.5 seconds.
2026-03-14 Implement main current sensing functionality
    Initialize peripherals for current sensing with INA228.
2026-03-14 Add INA228 driver for current sensing
2026-03-14 Add INA228 header file with register definitions
